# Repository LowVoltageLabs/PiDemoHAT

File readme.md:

Low Voltage Labs Pi Demo HAT
=============================================

Raspberry Pi HAT created for a 2015 Bay Area Maker Faire talk on creating Raspberry Pi HATs

The Low Voltage Labs Pi Demo HAT is a Raspberry Pi HAT that was created for a 2015 Bay Area Maker Faire talk: [Meta Pi: Design a Raspberry Pi HAT using KiCad running on the Raspberry Pi 2](https://makerfaire.com/maker/entry/50662/)
 The board was created to conform to the HAT standard as published by the Raspberry Pi foundation as of 2015. [https://github.com/raspberrypi/hats](https://github.com/raspberrypi/hats)
The board was never fully test, use at your own risk.
 
 Repository Contents
-------------------
* **/Hardware** - KiCAD design files 

License Information
-------------------
The hardware is released under [Creative Commons ShareAlike 4.0 International](https://creativecommons.org/licenses/by-sa/4.0/).

Distributed as-is, no warranty is given.

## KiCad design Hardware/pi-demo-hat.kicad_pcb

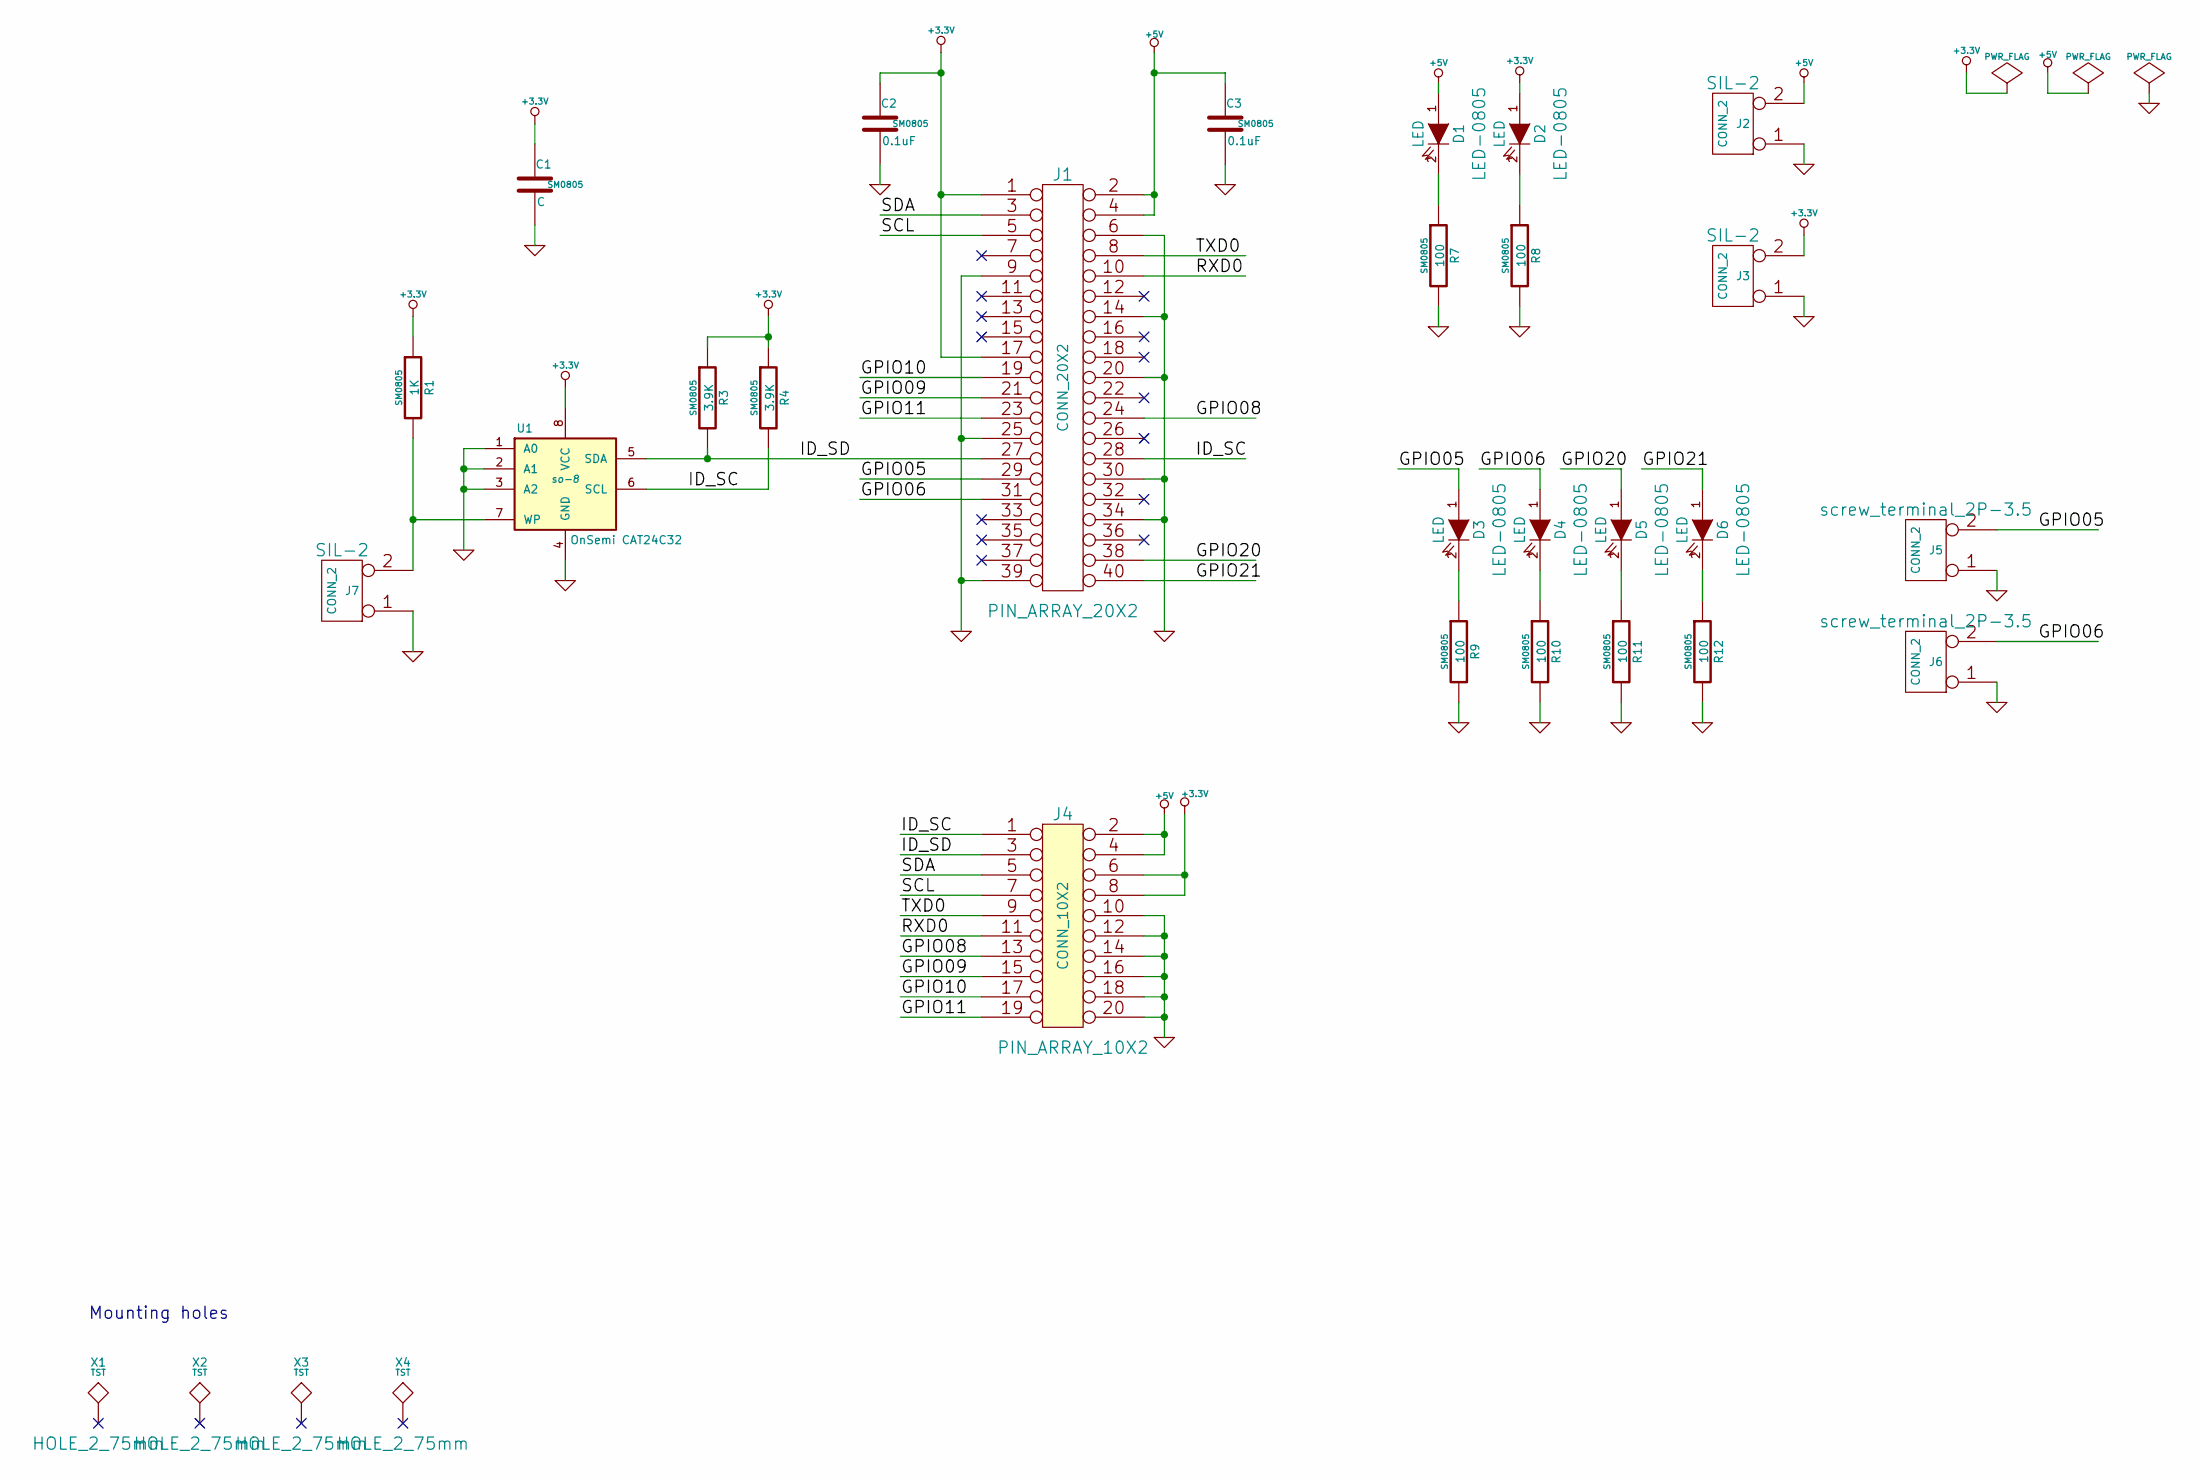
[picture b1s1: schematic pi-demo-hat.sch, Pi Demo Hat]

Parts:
C1: C; SM0805
C2, C3: 0.1uF; SM0805
D1, D2, D3, D4, D5, D6: LED; LED-0805
J1: CONN_20X2; PIN_ARRAY_20X2
J2, J3, J7: CONN_2; SIL-2
J4: CONN_10X2; PIN_ARRAY_10X2
J5, J6: CONN_2; screw_terminal_2P-3.5
R1: 1K; SM0805
R3, R4: 3.9K; SM0805
R7, R8, R9, R10, R11, R12: 100; SM0805
U1: OnSemi CAT24C32; so-8
X1, X2, X3, X4: TST; HOLE_2_75mm

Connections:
+3.3V: C1.1, C2.1, D2.1 (A), J1.1, J1.17, J3.2 (PM), J4.6, J4.8, R1.1, R3.1, R4.1, U1.8 (VCC)
+5V: C3.1, D1.1 (A), J1.2, J1.4, J2.2 (PM), J4.2, J4.4
/GPIO05: D3.1 (A), J1.29, J5.2 (PM)
/GPIO06: D4.1 (A), J1.31, J6.2 (PM)
/GPIO08: J1.24, J4.13
/GPIO09: J1.21, J4.15
/GPIO10: J1.19, J4.17
/GPIO11: J1.23, J4.19
/GPIO20: D5.1 (A), J1.38
/GPIO21: D6.1 (A), J1.40
/ID_SC: J1.28, J4.1, R4.2, U1.6 (SCL)
/ID_SD: J1.27, J4.3, R3.2, U1.5 (SDA)
/RXD0: J1.10, J4.11
/SCL: J1.5, J4.7
/SDA: J1.3, J4.5
/TXD0: J1.8, J4.9
GND: C1.2, C2.2, C3.2, J1.6, J1.9, J1.14, J1.20, J1.25, J1.30, J1.34, J1.39, J2.1, J3.1, J4.10, J4.12, J4.14, J4.16, J4.18, J4.20, J5.1, J6.1, J7.1, R7.2, R8.2, R9.2, R10.2, R11.2, R12.2, U1.1 (A0), U1.2 (A1), U1.3 (A2), U1.4 (GND)
unnamed: D6.2 (K), R12.1
unnamed: D3.2 (K), R9.1
unnamed: D4.2 (K), R10.1
unnamed: D5.2 (K), R11.1
unnamed: D2.2 (K), R8.1
unnamed: D1.2 (K), R7.1
unnamed: J7.2 (PM), R1.2, U1.7 (WP)

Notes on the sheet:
Mounting holes

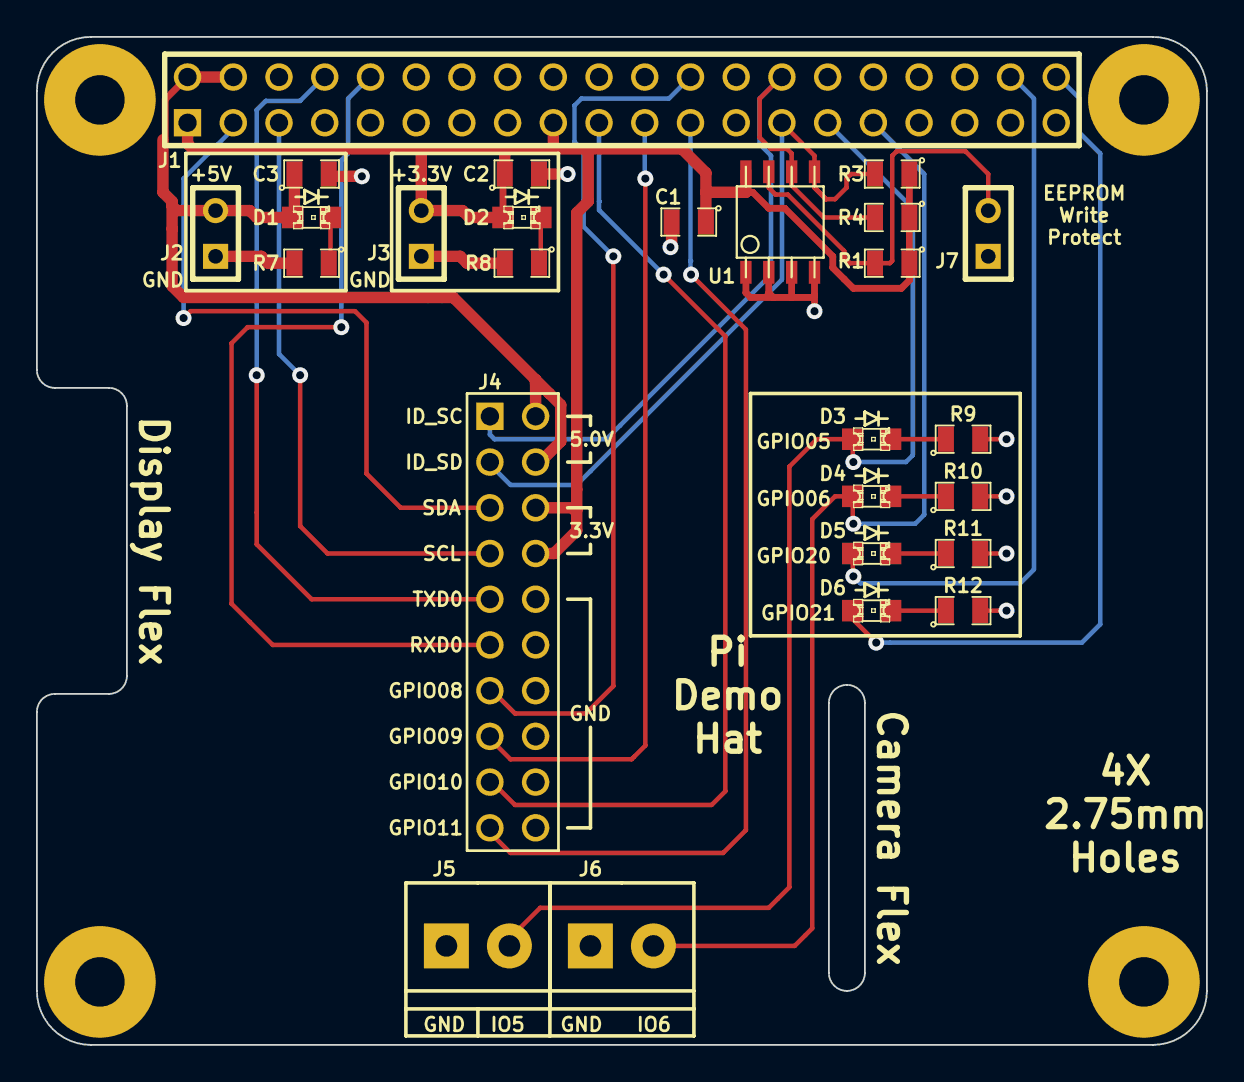
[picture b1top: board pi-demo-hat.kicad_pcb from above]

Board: 2 copper layers, 65.0 x 56.0 mm, 30 parts (0 on the bottom side), 24 nets.

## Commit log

2017-05-24 KiCAD files added
